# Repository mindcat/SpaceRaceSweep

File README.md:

# интеркосмос keyboard
My experience modifying and building a 34 key ferris sweep keyboard I themed after the Soviet-US space race...

## Synopsis
### [The Original Repo]() - please reference
### Parts List

Item | Notes | Amount | Total Cost
---|---|---|--:
<a href="">PCB Fabricator</a>|Other vendors also work...|5 (minimum order size- use 2)|$12
<a href="">Jade switches</a>|Choose whichever switch you like the feel of most- get a sample of a bunch if necessary, as this board is NOT hot-swappable. |34|$20
<a href="">Keycaps</a>|Keycaps with letters go in and out of stock often, and are more expensive.|34|$12-$35
<a href="">Elite-C V4</a>|Any microcontroller with this footprint works. I recommend USB C mc's, and look for bluetooth if you want a wireless keyboard.|2|$40 
<a href="">USB-C Cable</a>|You want data and power, but it doesn't have to handle much of either.||$8
<a href="">TRRS Jacks</a>|...|2|$1
<a href="">TRRS Cable</a>|...|1|$4

### Hardware
- Soldering Iron
- Tweezers [optional]
- Multimeter (not strictly, but VERY useful for checking electric continuity- if a key doesn't work, you can identify whether the issue is in the software, the pcb, the MC or switch pads, or the switch) [optional]
- Rosin (I didn't use any, but makes the microcontroller far easier to solder) [optional]
### Software
- KiCad
- QMK (command line, qmk toolbox, VIAL, et cetera- use what tools you need)
- Text editor or IDE [semi-optional]
- Adobe Illustrator (or a FOSS alternative) [optional]
### Skills
- 

# Process

## Inspiration
[Ben Vallack]() made a number of incredible videos on the ferris sweep (and it was his earlier videos reviewing the [gergoplex]() and [moonlander]() keyboards that led me to being interested in split keyboards and owning a moonlander myself, respectively). This linked one was vital to my problem solving and process, but I recommend checking out his other videos.

## Tools

## Design

## Build

## Software

Nothing unexpected if you're familiar with using [QMK](https://docs.qmk.fm/newbs) to make keymaps, though I'm sure all the GUI tools would work fine as well. 

## [OPTIONAL] 3D Printed Case

A couple weeks of knocking the keyboard halves around in my bag led me to designing a pretty simple clamshell 3D printed case for it. Layered on top of each other, the keyboard is ~32 mm thick. Edge to edge (lengthwise) it is ~120 mm wide. The first print was (as a factor of speed, carelessness, and limited experience with Fusion360) designed very imprecisely- working solely of those prior two measurements and a screenshot of the copper layer and edgecuts from KiCAD. 

Luckily, after printing it way too large the first time, I have a well printed and reliable case that I still don't use nearly enough. Unplugging the halves is minor, but somehow enough to discourage me from doing anything more than just putting the keyboard in a side pocket of my bag- especially since the case adds some cm that stop it from fitting in most convenient pockets in a bookbag. The Fusion files, as well as stls (v2 for FDM, v1), are included regardless...

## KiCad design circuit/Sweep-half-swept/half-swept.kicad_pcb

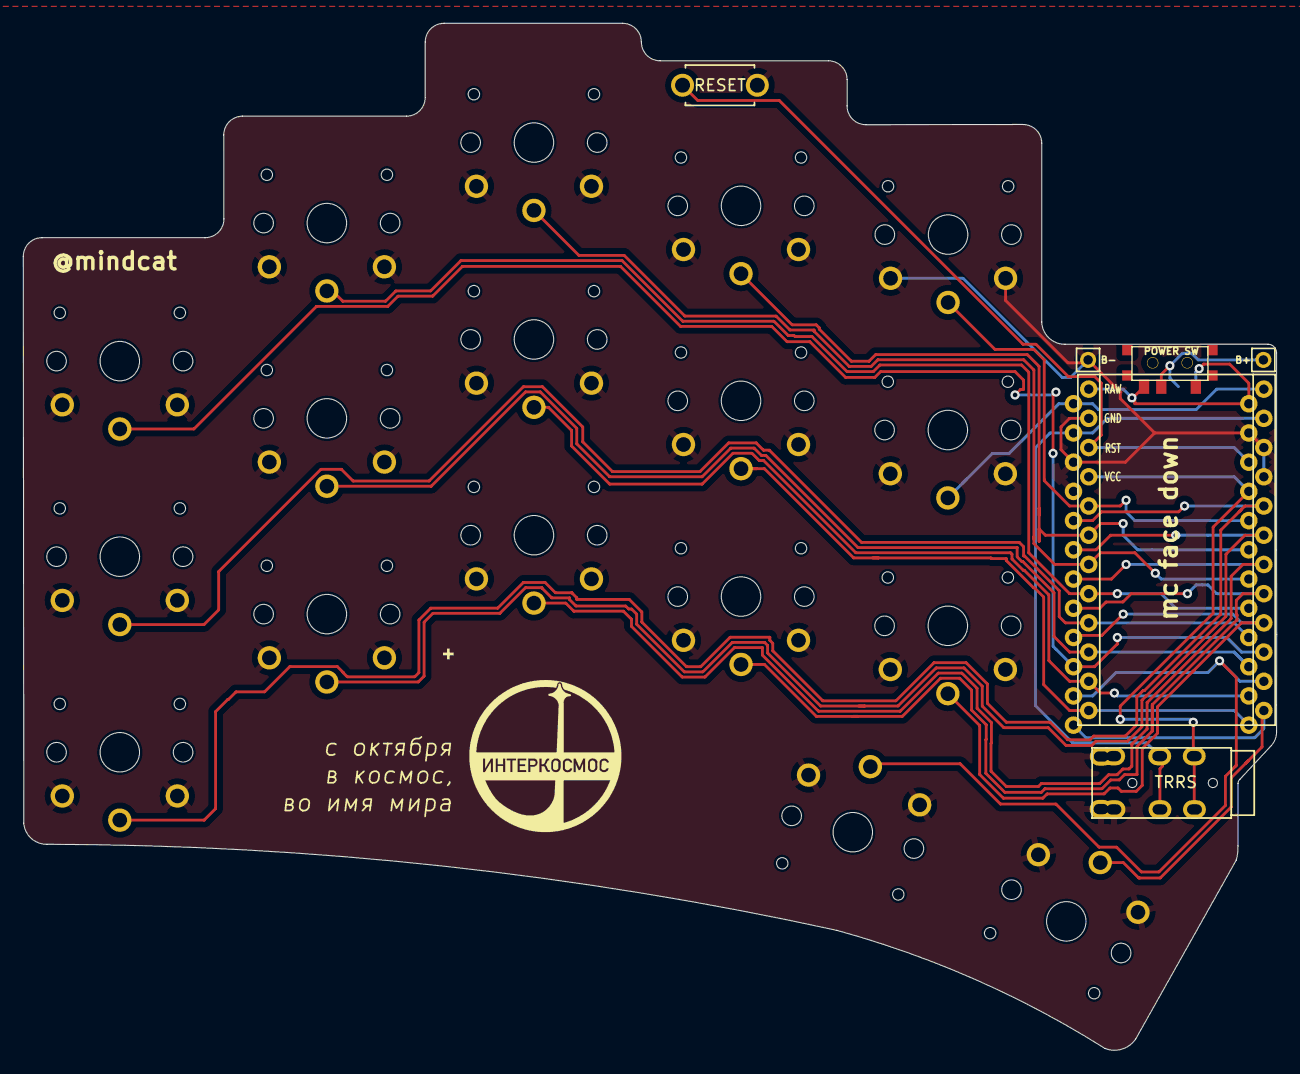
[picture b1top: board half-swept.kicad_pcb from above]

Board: 2 copper layers, 109.0 x 89.3 mm, 24 parts (1 on the bottom side), 23 nets.

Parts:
B+: MountingHole_Pad; 1pin_conn
B-: MountingHole_Pad; 1pin_conn
J2: AudioJack4dpb; TRRS-PJ-DPB2
POWER SW: SW_SPDT; SPDT_C128955
RSW1: SW_Push; ResetSW
SW2, SW3, SW4, SW5, SW6, SW8, SW9, SW10, SW11, SW12, SW14, SW15, SW16, SW17, SW18, SW20, SW21: SW_Push; SW_PG1350_rev_DPB
SW2#2: SW_SPDT; SPDT_C128955r
U1: ProMicro-kbd; ProMicro_v2

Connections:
BT+_r: B+.1, POWER SW.2, SW2#2.2
Switch1: SW2.1, U1.10
Switch2: SW3.1, U1.17
Switch3: SW4.1, U1.18
Switch4: SW5.1, U1.19
Switch5: SW6.1, U1.20
Switch6: SW8.1, U1.16
Switch7: SW9.1, U1.15
Switch8: SW10.1, U1.14
Switch9: SW11.1, U1.13
Switch10: SW12.1, U1.1, U1.Е
Switch11: SW14.1, U1.5
Switch12: SW15.1, U1.6
Switch13: SW16.1, U1.7
Switch14: SW17.1, U1.8
Switch15: SW18.1, U1.9
Switch16: SW21.1, U1.11
Switch17: SW20.1, U1.12
Switch18: J2.R1, U1.2
gnd: B-.1, J2.S, J2.T, RSW1.1, SW2.2, SW3.2, SW4.2, SW5.2, SW6.2, SW8.2, SW9.2, SW10.2, SW11.2, SW12.2, SW14.2, SW15.2, SW16.2, SW17.2, SW18.2, SW20.2, SW21.2, U1.3, U1.4, U1.23
raw: POWER SW.3, SW2#2.3, U1.24
reset: RSW1.2, U1.22
vcc: J2.R2, U1.21

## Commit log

2024-02-06 added c code- keymap, rules, et cetera
2025-01-23 leagues worth of updates
